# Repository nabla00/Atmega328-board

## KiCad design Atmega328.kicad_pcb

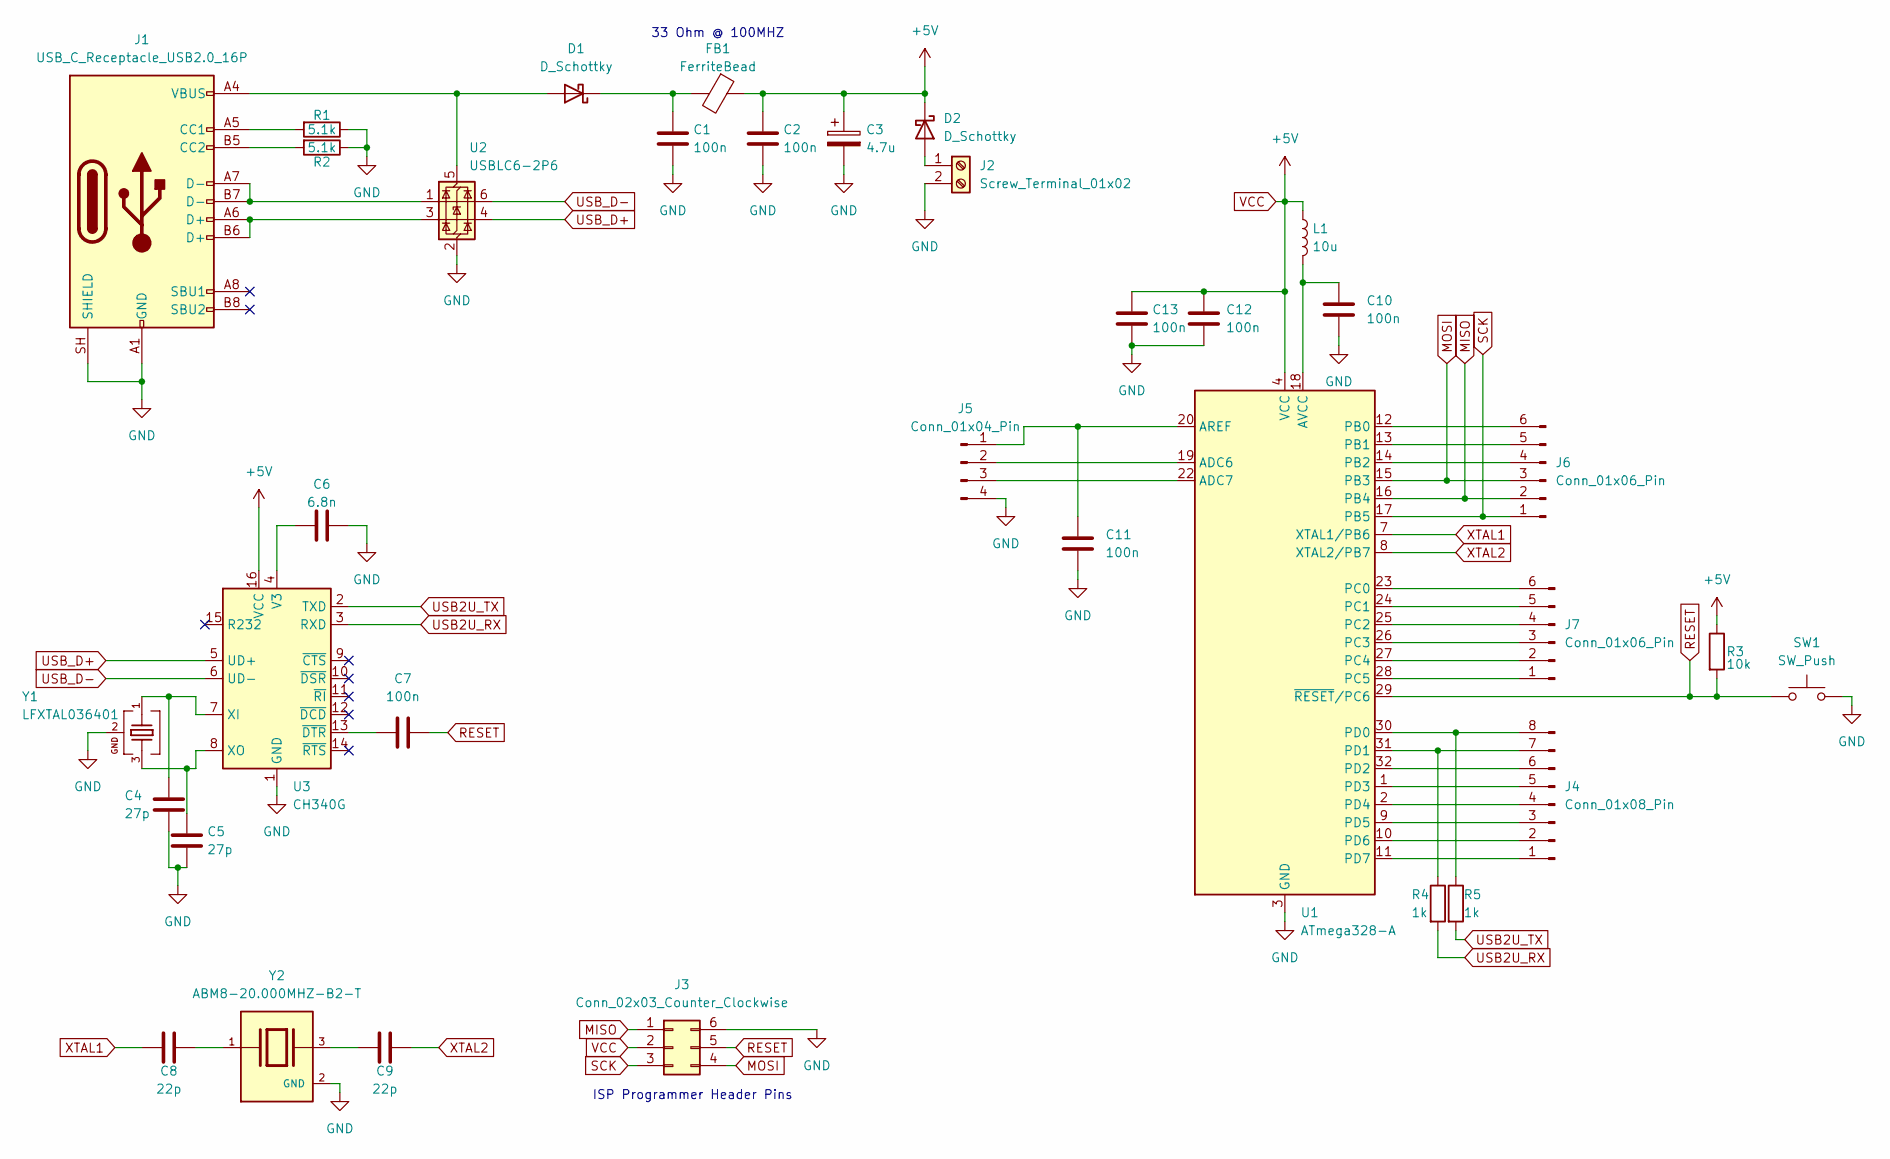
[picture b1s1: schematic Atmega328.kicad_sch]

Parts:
C1, C2, C7, C10, C11, C12, C13: 100n; C_0805_2012Metric_Pad1.18x1.45mm_HandSolder
C3: 4.7u; CP_Radial_D6.3mm_P2.50mm
C4, C5: 27p; C_0805_2012Metric_Pad1.18x1.45mm_HandSolder
C6: 6.8n; C_0805_2012Metric_Pad1.18x1.45mm_HandSolder
C8, C9: 22p; C_0805_2012Metric_Pad1.18x1.45mm_HandSolder
D1: D_Schottky; C_0805_2012Metric_Pad1.18x1.45mm_HandSolder
D2: D_Schottky; D_0805_2012Metric_Pad1.15x1.40mm_HandSolder
FB1: FerriteBead; WE-CBF_0805_W4.0
J1: USB_C_Receptacle_USB2.0_16P; USB_C_Receptacle_Palconn_UTC16-G
J2: Screw_Terminal_01x02; TerminalBlock_Xinya_XY308-2.54-2P_1x02_P2.54mm_Horizontal
J3: Conn_02x03_Counter_Clockwise; PinHeader_2x03_P2.54mm_Vertical
J4: Conn_01x08_Pin; PinHeader_1x08_P2.54mm_Vertical
J5: Conn_01x04_Pin; PinHeader_1x04_P2.54mm_Vertical
J6, J7: Conn_01x06_Pin; PinHeader_1x06_P2.54mm_Vertical
L1: 10u; L_0805_2012Metric_Pad1.05x1.20mm_HandSolder
R1, R2: 5.1k; R_0805_2012Metric_Pad1.20x1.40mm_HandSolder
R3: 10k; R_0805_2012Metric_Pad1.20x1.40mm_HandSolder
R4, R5: 1k; R_0805_2012Metric_Pad1.20x1.40mm_HandSolder
SW1: SW_Push; SW_Push_1P1T_NO_CK_KMR2
U1: ATmega328-A; TQFP-32_7x7mm_P0.8mm
U2: USBLC6-2P6; SOT-666
U3: CH340G; SOIC-16_3.9x9.9mm_P1.27mm
Y1: LFXTAL036401; WE-XTAL_LFXTAL036401
Y2: ABM8-20.000MHZ-B2-T; XTAL_ABM8-20.000MHZ-B2-T; PARTREV 44041

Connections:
GND: C1.2, C2.2, C3.2, C4.1, C5.1, C6.2, C10.2, C11.2, C12.2, C13.2, J1.A1 (GND), J1.A12 (GND), J1.B1 (GND), J1.B12 (GND), J1.SH (SHIELD), J2.2, J3.6, J5.4, R1.1, R2.1, SW1.2, U1.3 (GND), U1.5 (GND), U1.21 (GND), U2.2 (GND), U3.1 (GND), Y1.2, Y1.4, Y2.2 (GND), Y2.4 (GND)
MISO: J3.1, J6.2, U1.16 (PB4)
MOSI: J3.4, J6.3, U1.15 (PB3)
unnamed: C8.1, Y2.1
unnamed: C9.2, Y2.3
unnamed: D1.2 (A), J1.A4 (VBUS), J1.A9 (VBUS), J1.B4 (VBUS), J1.B9 (VBUS), U2.5 (VBUS)
unnamed: C1.1, D1.1 (K), FB1.2
unnamed: D2.2 (A), J2.1
unnamed: J1.A5 (CC1), R1.2
unnamed: J1.B5 (CC2), R2.2
unnamed: J1.A6 (D+), J1.B6 (D+), U2.3 (I/O2)
unnamed: J1.A7 (D-), J1.B7 (D-), U2.1 (I/O1)
unnamed: J4.1, U1.11 (PD7)
unnamed: J4.2, U1.10 (PD6)
unnamed: J4.3, U1.9 (PD5)
unnamed: J4.4, U1.2 (PD4)
unnamed: J4.5, U1.1 (PD3)
unnamed: J4.6, U1.32 (PD2)
unnamed: J4.7, R4.1, U1.31 (PD1)
unnamed: J4.8, R5.1, U1.30 (PD0)
unnamed: C11.1, J5.1, U1.20 (AREF)
unnamed: J5.2, U1.19 (ADC6)
unnamed: J5.3, U1.22 (ADC7)
unnamed: J6.4, U1.14 (PB2)
unnamed: J6.5, U1.13 (PB1)
unnamed: J6.6, U1.12 (PB0)
unnamed: J7.1, U1.28 (PC5)
unnamed: J7.2, U1.27 (PC4)
unnamed: J7.3, U1.26 (PC3)
unnamed: J7.4, U1.25 (PC2)
unnamed: J7.5, U1.24 (PC1)
unnamed: J7.6, U1.23 (PC0)
unnamed: C10.1, L1.2, U1.18 (AVCC)
unnamed: C6.1, U3.4 (V3)
unnamed: C4.2, U3.7 (XI), Y1.1
unnamed: C5.2, U3.8 (XO), Y1.3
unnamed: C7.2, U3.13 (~DTR)
RESET: C7.1, J3.5, R3.2, SW1.1, U1.29 (~RESET/PC6)
SCK: J3.3, J6.1, U1.17 (PB5)
USB2U_RX: R4.2, U3.3 (RXD)
USB2U_TX: R5.2, U3.2 (TXD)
USB_D+: U2.4 (I/O2), U3.5 (UD+)
USB_D-: U2.6 (I/O1), U3.6 (UD-)
VCC: C2.1, C3.1, C12.1, C13.1, D2.1 (K), FB1.1, J3.2, L1.1, R3.1, U1.4 (VCC), U1.6 (VCC), U3.16 (VCC)
XTAL1: C8.2, U1.7 (XTAL1/PB6)
XTAL2: C9.1, U1.8 (XTAL2/PB7)

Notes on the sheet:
33 Ohm @ 100MHZ
ISP Programmer Header Pins

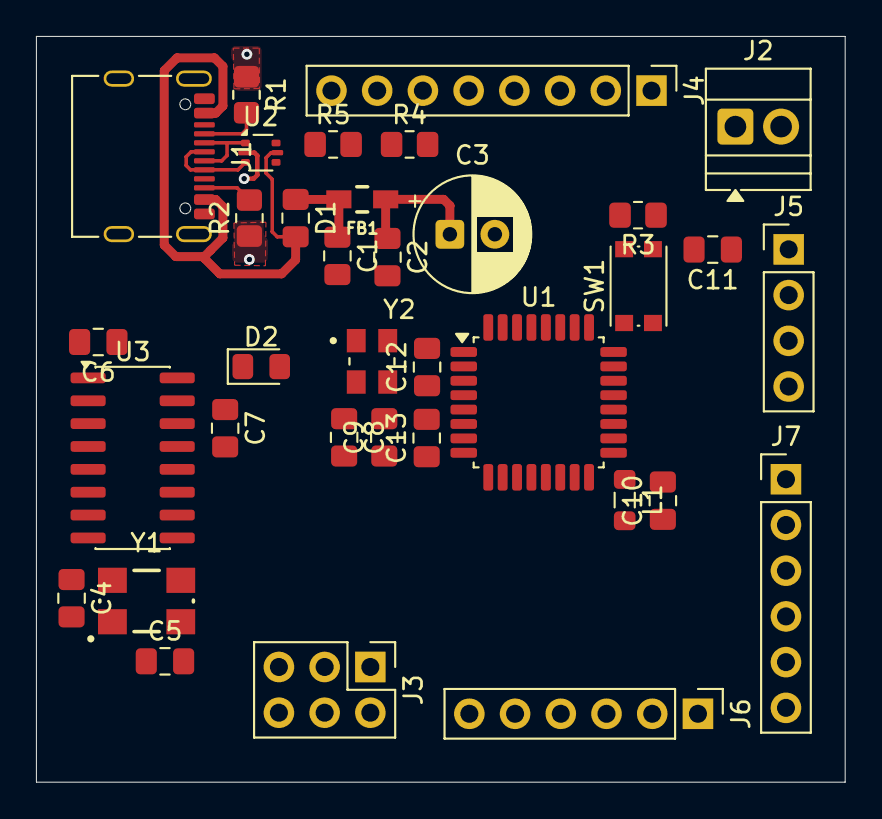
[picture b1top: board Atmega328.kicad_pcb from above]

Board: 4 copper layers, 44.9 x 41.4 mm, 35 parts (0 on the bottom side), 46 nets.
